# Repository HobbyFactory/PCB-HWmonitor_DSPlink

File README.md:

# HWmonitor & DSPlink

This is a debug tool, for visualizing digital signals from DSP or Microcontroller on Oscilloscope screen. In adition contains USB<->Serial converter to allow debug 
communication with target device.

Heart of the device is fast SPI D/A converter AD5324ARMZ, converting 4 channels into analog values, post processed by operational amplifiers. High voltage 8kVrms (ISO78XXDWW) galvanic isolation is provided between all inputs/outputs, to ensure safe debug experience, especially with high voltage power converters. 

Schematic, PCB project in KiCad and BOM are included in this repository. Device does not require any firmware for operation.

Model of the box optimized for 3D printer you can find here:
https://www.thingiverse.com/thing:4769601

If you are interested, send me the message, I still have some PCBs left from JLC.PCB. Assembled and tested version is available too.

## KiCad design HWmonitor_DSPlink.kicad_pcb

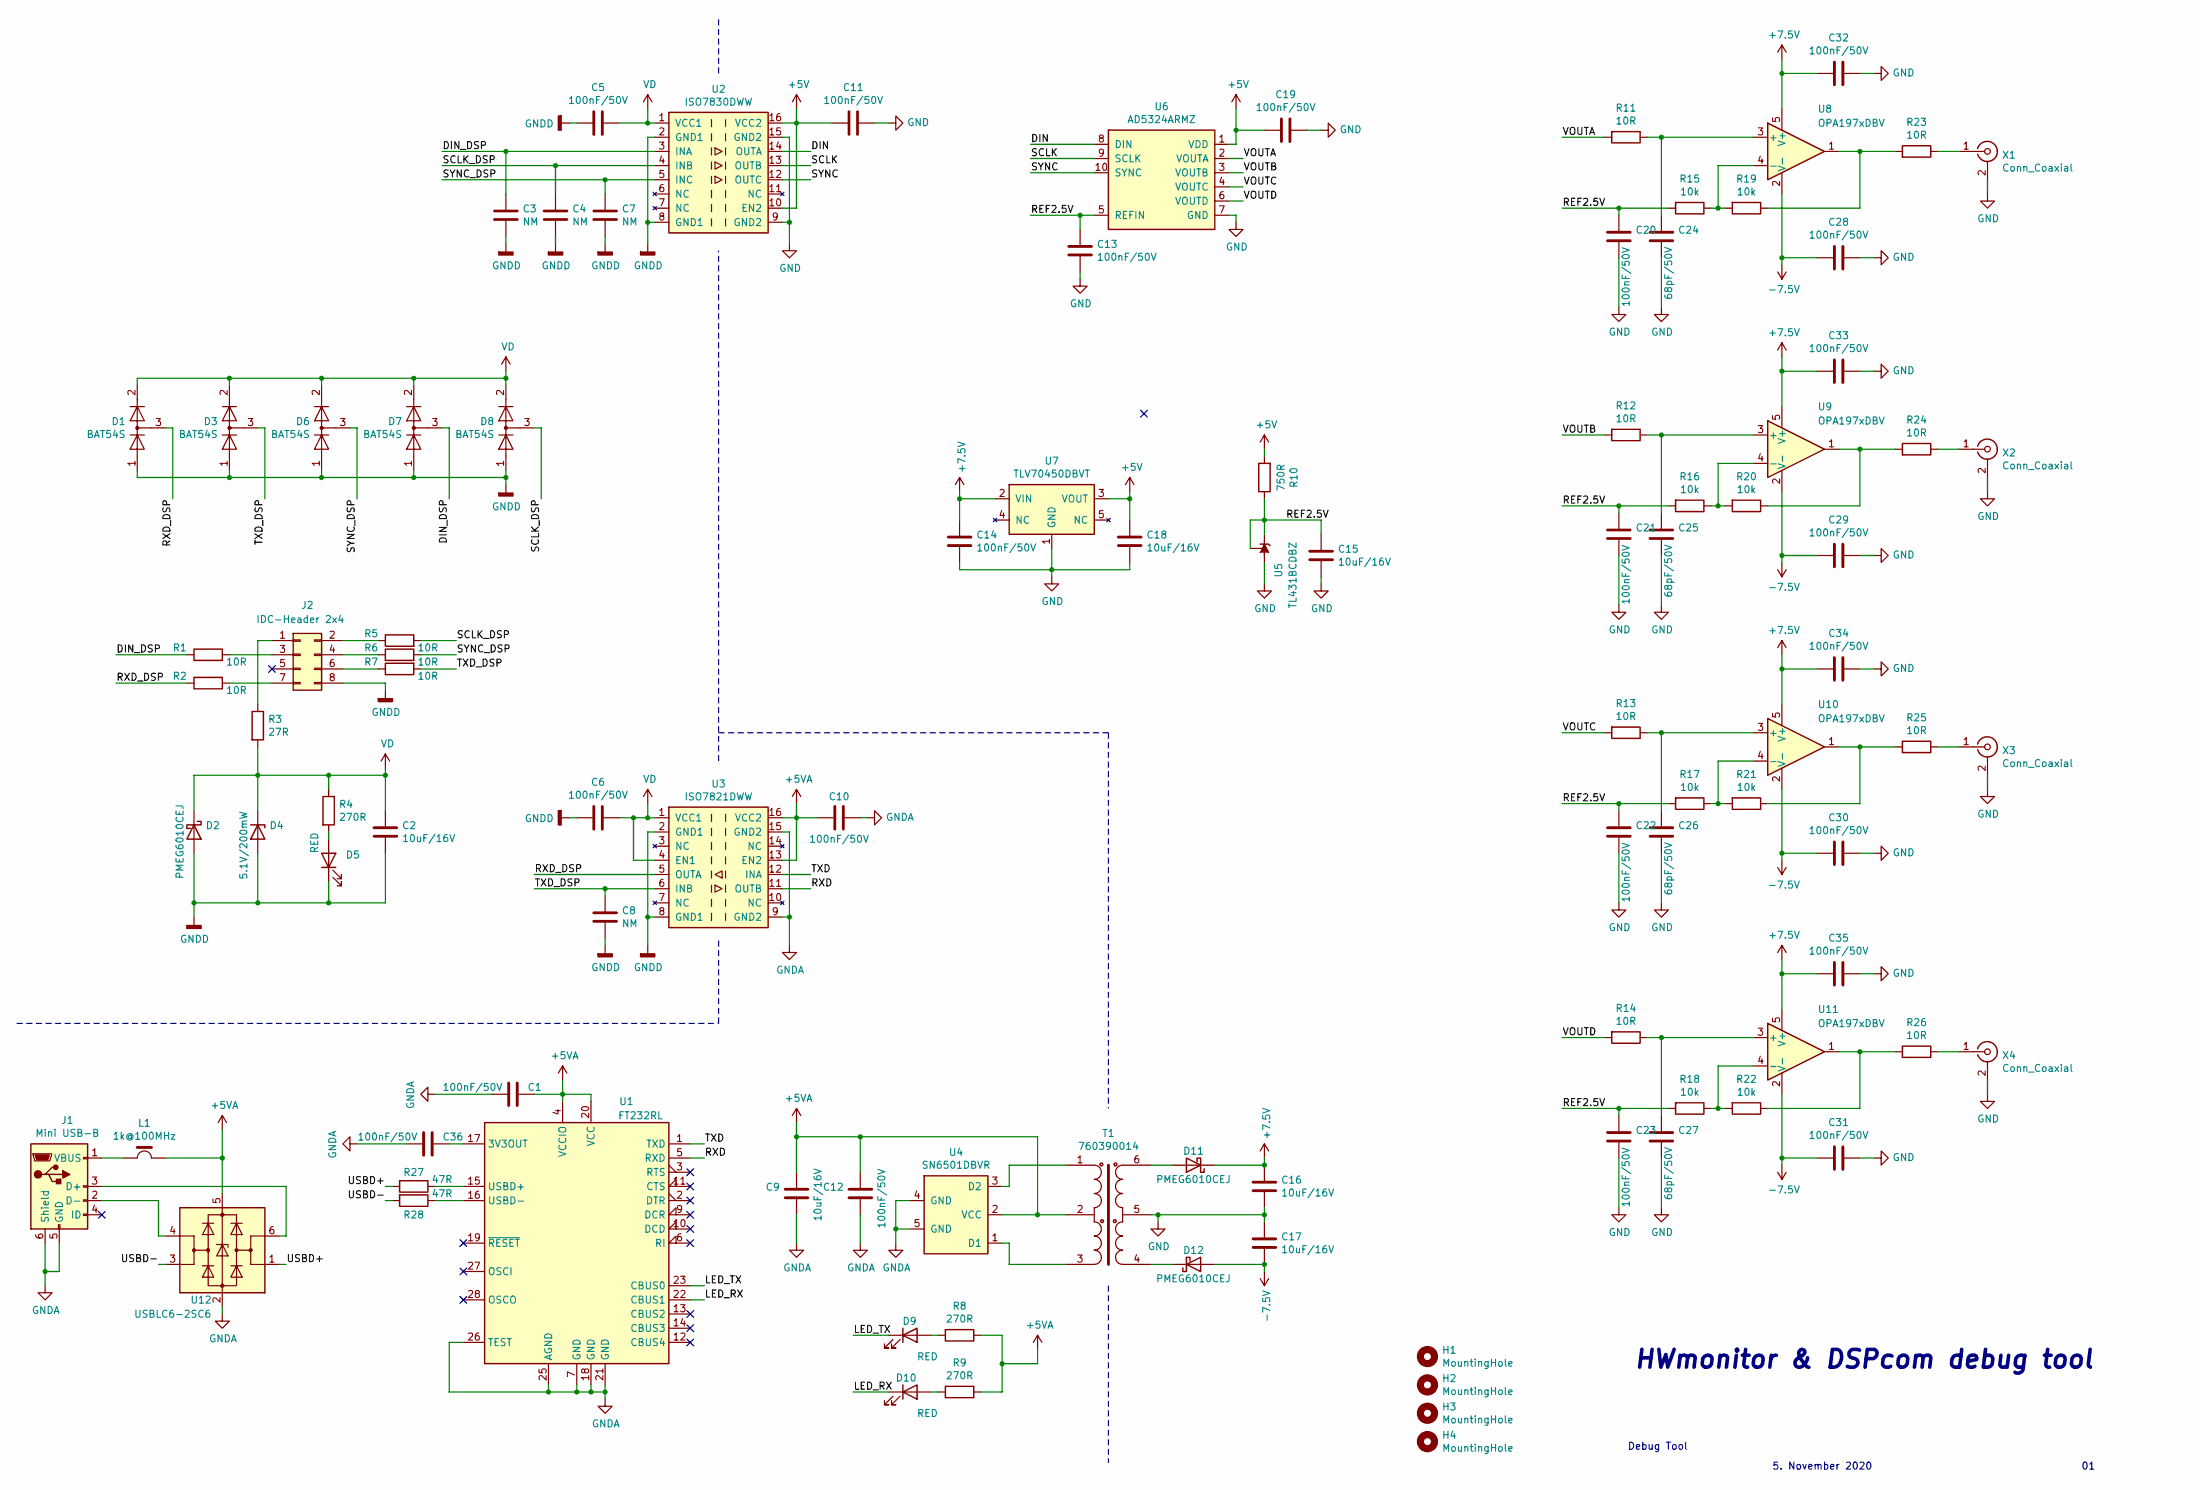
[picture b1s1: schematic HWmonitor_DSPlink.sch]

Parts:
C1, C5, C6, C10, C11, C12, C13, C14, C19, C20, C21, C22, C23, C28, C29, C30, C31, C32, C33, C34, C35, C36: 100nF/50V; C_0603_1608Metric
C2, C9, C15, C16, C17, C18: 10uF/16V; C_0805_2012Metric; MPN CC0805MKX7R7BB106
C3, C4, C7, C8: NM; C_0603_1608Metric
C24, C25, C26, C27: 68pF/50V; C_0603_1608Metric
D1, D3, D6, D7, D8: BAT54S; SOT-23; MPN BAT54S
D2, D11, D12: PMEG6010CEJ; D_SOD-323F; MPN PMEG6010CEJ
D4: 5.1V/200mW; D_SOD-323F; MPN MM3Z5V1C
D5, D9, D10: RED; LED_D3.0mm_FlatTop; MPN WP424SRDT
H1, H2, H3, H4: MountingHole; MountingHole_3.2mm_M3; MPN PHANTOM
J1: Mini USB-B; USB_Mini-B_Lumberg_2486_01_Horizontal; MPN 65100516121
J2: IDC-Header 2x4; IDC-Header_2x04_P2.54mm_Vertical; MPN 61200821621
L1: 1k@100MHz; L_0603_1608Metric; MPN 742792664
R1, R2, R5, R6, R7, R11, R12, R13, R14, R23, R24, R25, R26: 10R; R_0603_1608Metric
R3: 27R; R_0603_1608Metric
R4, R8, R9: 270R; R_0603_1608Metric
R10: 750R; R_0603_1608Metric
R15, R16, R17, R18, R19, R20, R21, R22: 10k; R_0603_1608Metric
R27, R28: 47R; R_0603_1608Metric
T1: 760390014; Wuerth_760390014; MPN 760390014
U1: FT232RL; SSOP-28_5.3x10.2mm_P0.65mm; MPN FT232RL
U2: ISO7830DWW; SOIC-16DWW; MPN ISO7830DWW
U3: ISO7821DWW; SOIC-16DWW; MPN ISO7821DWW
U4: SN6501DBVR; SOT-23-5; MPN SN6501DBVR
U5: TL431BCDBZ; SOT-23; MPN TL431BCDBZ
U6: AD5324ARMZ; MSOP-10_3x3mm_P0.5mm; MPN AD5324ARMZ
U7: TLV70450DBVT; SOT-23-5; MPN TLV70450DBVT
U8, U9, U10, U11: OPA197xDBV; SOT-23-5; MPN OPA197IDBV
U12: USBLC6-2SC6; SOT-23-6; MPN USBLC6-2SC6
X1, X2, X3, X4: Conn_Coaxial; Connector_131-3701-301; MPN 131-3701-301

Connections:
+5V: C11.1, C18.2, C19.1, R10.2, U2.10 (EN2), U2.16 (VCC2), U6.1 (VDD), U7.3 (VOUT)
+5VA: C1.2, C9.2, C10.1, C12.1, L1.2, R8.1, R9.1, T1.2, U1.4 (VCCIO), U1.20 (VCC), U3.13 (EN2), U3.16 (VCC2), U4.2 (VCC), U12.5 (VBUS)
+7.5V: C14.2, C16.2, C32.2, C33.2, C34.2, C35.2, D11.1 (K), U7.2 (VIN), U8.5 (V+), U9.5 (V+), U10.5 (V+), U11.5 (V+)
-7.5V: C17.1, C28.2, C29.2, C30.2, C31.2, D12.2 (A), U8.2 (V-), U9.2 (V-), U10.2 (V-), U11.2 (V-)
/DIN: U2.14 (OUTA), U6.8 (DIN)
/DIN_DSP: C3.2, D7.3 (K), R1.1, U2.3 (INA)
/LED_RX: D10.1 (K), U1.22 (CBUS1)
/LED_TX: D9.1 (K), U1.23 (CBUS0)
/REF2.5V: C13.2, C15.2, C20.2, C21.2, C22.2, C23.2, R10.1, R15.2, R16.2, R17.2, R18.2, U5.1 (K), U5.2 (REF), U6.5 (REFIN)
/RXD: U1.5 (RXD), U3.11 (OUTB)
/RXD_DSP: D1.3 (K), R2.1, U3.5 (OUTA)
/SCLK: U2.13 (OUTB), U6.9 (SCLK)
/SCLK_DSP: C4.2, D8.3 (K), R5.2, U2.4 (INB)
/SYNC: U2.12 (OUTC), U6.10 (SYNC)
/SYNC_DSP: C7.2, D6.3 (K), R6.2, U2.5 (INC)
/TXD: U1.1 (TXD), U3.12 (INA)
/TXD_DSP: C8.2, D3.3 (K), R7.2, U3.6 (INB)
/USBD+: R27.2, U12.1 (I/O1)
/USBD-: R28.2, U12.3 (I/O2)
/VOUTA: R11.2, U6.2 (VOUTA)
/VOUTB: R12.2, U6.3 (VOUTB)
/VOUTC: R13.2, U6.4 (VOUTC)
/VOUTD: R14.2, U6.6 (VOUTD)
GND: C11.2, C13.1, C14.1, C15.1, C16.1, C17.2, C18.1, C19.2, C20.1, C21.1, C22.1, C23.1, C24.1, C25.1, C26.1, C27.1, C28.1, C29.1, C30.1, C31.1, C32.1, C33.1, C34.1, C35.1, T1.5, U2.9 (GND2), U2.15 (GND2), U5.3 (A), U6.7 (GND), U7.1 (GND), X1.2 (Ext), X2.2 (Ext), X3.2 (Ext), X4.2 (Ext)
GNDA: C1.1, C9.1, C10.2, C12.2, C36.1, J1.5 (GND), J1.6 (Shield), U1.7 (GND), U1.18 (GND), U1.21 (GND), U1.25 (AGND), U1.26 (TEST), U3.9 (GND2), U3.15 (GND2), U4.4 (GND), U4.5 (GND), U12.2 (GND)
GNDD: C2.1, C3.1, C4.1, C5.1, C6.1, C7.1, C8.1, D1.1 (K), D2.2 (A), D3.1 (K), D4.2 (A), D5.1 (K), D6.1 (K), D7.1 (K), D8.1 (K), J2.8, U2.2 (GND1), U2.8 (GND1), U3.2 (GND1), U3.8 (GND1)
unnamed: C24.2, R11.1, U8.3 (+)
unnamed: C25.2, R12.1, U9.3 (+)
unnamed: C26.2, R13.1, U10.3 (+)
unnamed: C27.2, R14.1, U11.3 (+)
unnamed: C36.2, U1.17 (3V3OUT)
unnamed: D5.2 (A), R4.2
unnamed: D9.2 (A), R8.2
unnamed: D10.2 (A), R9.2
unnamed: D11.2 (A), T1.6
unnamed: D12.1 (K), T1.4
unnamed: J1.1 (VBUS), L1.1
unnamed: J1.2 (D-), U12.4 (I/O2)
unnamed: J1.3 (D+), U12.6 (I/O1)
unnamed: J2.1, R3.1
unnamed: J2.2, R5.1
unnamed: J2.3, R1.2
unnamed: J2.4, R6.1
unnamed: J2.6, R7.1
unnamed: J2.7, R2.2
unnamed: R15.1, R19.2, U8.4 (-)
unnamed: R16.1, R20.2, U9.4 (-)
unnamed: R17.1, R21.2, U10.4 (-)
unnamed: R18.1, R22.2, U11.4 (-)
unnamed: R19.1, R23.2, U8.1
unnamed: R20.1, R24.2, U9.1
unnamed: R21.1, R25.2, U10.1
unnamed: R22.1, R26.2, U11.1
unnamed: R23.1, X1.1 (In)
unnamed: R24.1, X2.1 (In)
unnamed: R25.1, X3.1 (In)
unnamed: R26.1, X4.1 (In)
unnamed: R27.1, U1.15 (USBD+)
unnamed: R28.1, U1.16 (USBD-)
unnamed: T1.1, U4.3 (D2)
unnamed: T1.3, U4.1 (D1)
VD: C2.2, C5.2, C6.2, D1.2 (A), D2.1 (K), D3.2 (A), D4.1 (K), D6.2 (A), D7.2 (A), D8.2 (A), R3.2, R4.1, U2.1 (VCC1), U3.1 (VCC1), U3.4 (EN1)

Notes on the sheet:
5. November 2020
Debug Tool
HWmonitor & DSPcom debug tool

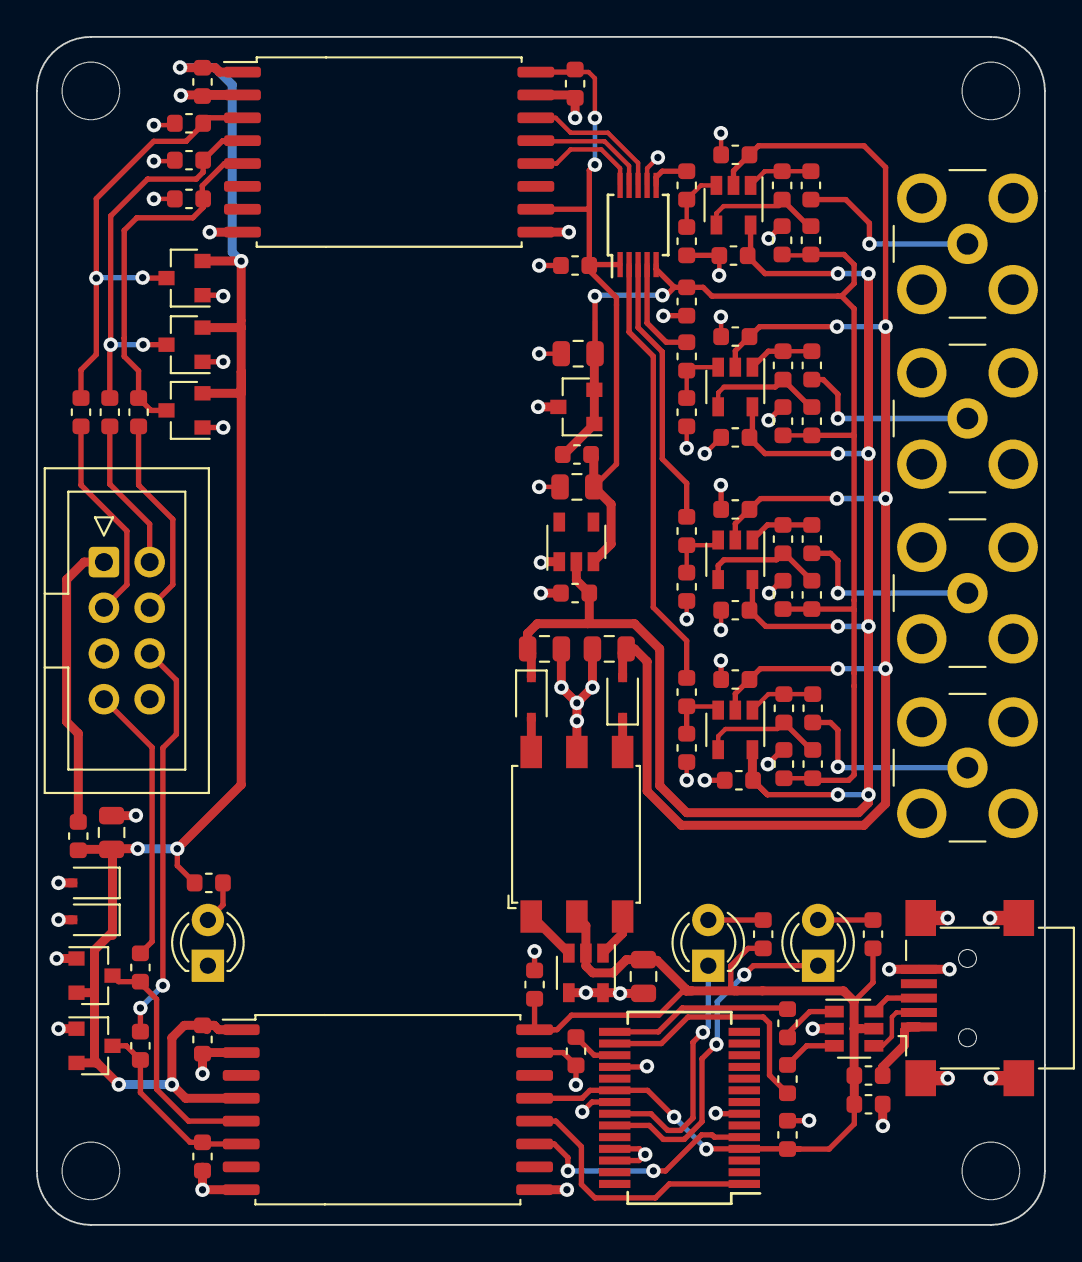
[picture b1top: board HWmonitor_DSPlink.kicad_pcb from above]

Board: 2 copper layers, 56.0 x 66.0 mm, 100 parts (0 on the bottom side), 62 nets.

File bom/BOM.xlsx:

Item | Qty | Reference(s) | Value | LibPart | Footprint | Datasheet | MPN
1 | 22 | C1, C5, C6, C10, C11, C12, C13, C14, C19, C20, C21, C22, C23, C28, C29, C30, C3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 | 100nF/50V | Device:C | Capacitor_SMD:C_0603_1608Metric | ~
2 | 6 | C2, C9, C15, C16, C17, C18 | 10uF/16V | Device:C | Capacitor_SMD:C_0805_2012Metric | ~ | CC0805MKX7R7BB106
3 | 4 | C3, C4, C7, C8 | - | Device:C | Capacitor_SMD:C_0603_1608Metric | ~ | -
4 | 4 | C24, C25, C26, C27 | 68pF/50V | Device:C | Capacitor_SMD:C_0603_1608Metric | ~
5 | 5 | D1, D3, D6, D7, D8 | BAT54S | Diode:BAV99 | Package_TO_SOT_SMD:SOT-23 | https://assets.nexperia.com/documents/data-sheet/BAV99_SER.pdf | BAT54S
6 | 3 | D2, D11, D12 | PMEG6010CEJ | Device:D_Schottky | Diode_SMD:D_SOD-323F | ~ | PMEG6010CEJ
7 | 1 | D4 | 5.1V/200mW | Device:D_Zener | Diode_SMD:D_SOD-323F | ~ | MM3Z5V1C
8 | 3 | D5, D9, D10 | RED | Device:LED | LED_THT:LED_D3.0mm_FlatTop | ~ | WP424SRDT
9 | 4 | H1, H2, H3, H4 | MountingHole | Mechanical:MountingHole | MountingHole:MountingHole_3.2mm_M3 | ~ | PHANTOM
10 | 1 | J1 | Mini USB-B | Connector:USB_B_Mini | Connector_USB:USB_Mini-B_Lumberg_2486_01_Horizontal | ~ | 65100516121
11 | 1 | J2 | IDC-Header 2x4 | Connector_Generic:Conn_02x04_Odd_Even | Connector_IDC:IDC-Header_2x04_P2.54mm_Vertical | ~ | 61200821621
12 | 1 | L1 | 1k@100MHz | #MyLibrary:Ferrite_Bead | Inductor_SMD:L_0603_1608Metric |  | 742792664
13 | 13 | R1, R2, R5, R6, R7, R11, R12, R13, R14, R23, R24, R25, R26 | 10R | Device:R | Resistor_SMD:R_0603_1608Metric | ~
14 | 1 | R3 | 27R | Device:R | Resistor_SMD:R_0603_1608Metric | ~
15 | 2 | R4, R8, R9 | 270R | Device:R | Resistor_SMD:R_0603_1608Metric | ~
16 | 1 | R10 | 750R | Device:R | Resistor_SMD:R_0603_1608Metric | ~
17 | 8 | R15, R16, R17, R18, R19, R20, R21, R22 | 10k | Device:R | Resistor_SMD:R_0603_1608Metric | ~
18 | 2 | R27, R28 | 47R | Device:R | Resistor_SMD:R_0603_1608Metric | ~
19 | 1 | T1 | 760390014 | #MyLibrary:760390014 | #MyLibrary:Wuerth_760390014 | https://www.mouser.ch/datasheet/2/445/760390014-221199.pdf | 760390014
20 | 1 | U1 | FT232RL | Interface_USB:FT232RL | Package_SO:SSOP-28_5.3x10.2mm_P0.65mm | https://www.ftdichip.com/Support/Documents/DataSheets/ICs/DS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 | FT232RL
21 | 1 | U2 | ISO7830DWW | #MyLibrary:ISO7830DWW | #MyLibrary:SOIC-16DWW |  | ISO7830DWW
22 | 1 | U3 | ISO7821DWW | #MyLibrary:ISO7821DWW | #MyLibrary:SOIC-16DWW |  | ISO7821DWW
23 | 1 | U4 | SN6501DBVR | #MyLibrary:SN6501 | Package_TO_SOT_SMD:SOT-23-5 |  | SN6501DBVR
24 | 1 | U5 | TL431BCDBZ | Reference_Voltage:TL431DBZ | Package_TO_SOT_SMD:SOT-23 | http://www.ti.com/lit/ds/symlink/tl431.pdf | TL431BCDBZ
25 | 1 | U6 | AD5324ARMZ | #MyLibrary:AD5324ARMZ | Package_SO:MSOP-10_3x3mm_P0.5mm |  | AD5324ARMZ
26 | 1 | U7 | TLV70450DBVT | #MyLibrary:TLV70450DBVT | Package_TO_SOT_SMD:SOT-23-5 |  | TLV70450DBVT
27 | 4 | U8, U9, U10, U11 | OPA197xDBV | Amplifier_Operational:OPA197xDBV | Package_TO_SOT_SMD:SOT-23-5 | http://www.ti.com/lit/ds/symlink/opa197.pdf | OPA197IDBV
28 | 1 | U12 | USBLC6-2SC6 | Power_Protection:USBLC6-2SC6 | Package_TO_SOT_SMD:SOT-23-6 | https://www.st.com/resource/en/datasheet/usblc6-2.pdf | USBLC6-2SC6
29 | 4 | X1, X2, X3, X4 | Conn_Coaxial | Connector:Conn_Coaxial | #MyLibrary:Connector_131-3701-301 | ~ | 131-3701-301 OR 731000103

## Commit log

2020-11-05 Schematic drawn!
2020-11-14 all footprints assigned
2020-11-20 initial placement
2020-12-05 placement, added USB input protection
2020-12-11 some initial routing done
2020-12-12 two parts routed
2020-12-13 routing finished, added all MPNs
2020-12-13 pdf schematic
2020-12-20 modified layout ftdi chip, added 3.3V capacitor
2020-12-20 last modifications, documents generated
2020-12-20 3D snapshot
2021-01-13 Added assembly drawing
2021-02-12 BOM bug, LED resistor to 270R
2021-02-20 Added block diagram
